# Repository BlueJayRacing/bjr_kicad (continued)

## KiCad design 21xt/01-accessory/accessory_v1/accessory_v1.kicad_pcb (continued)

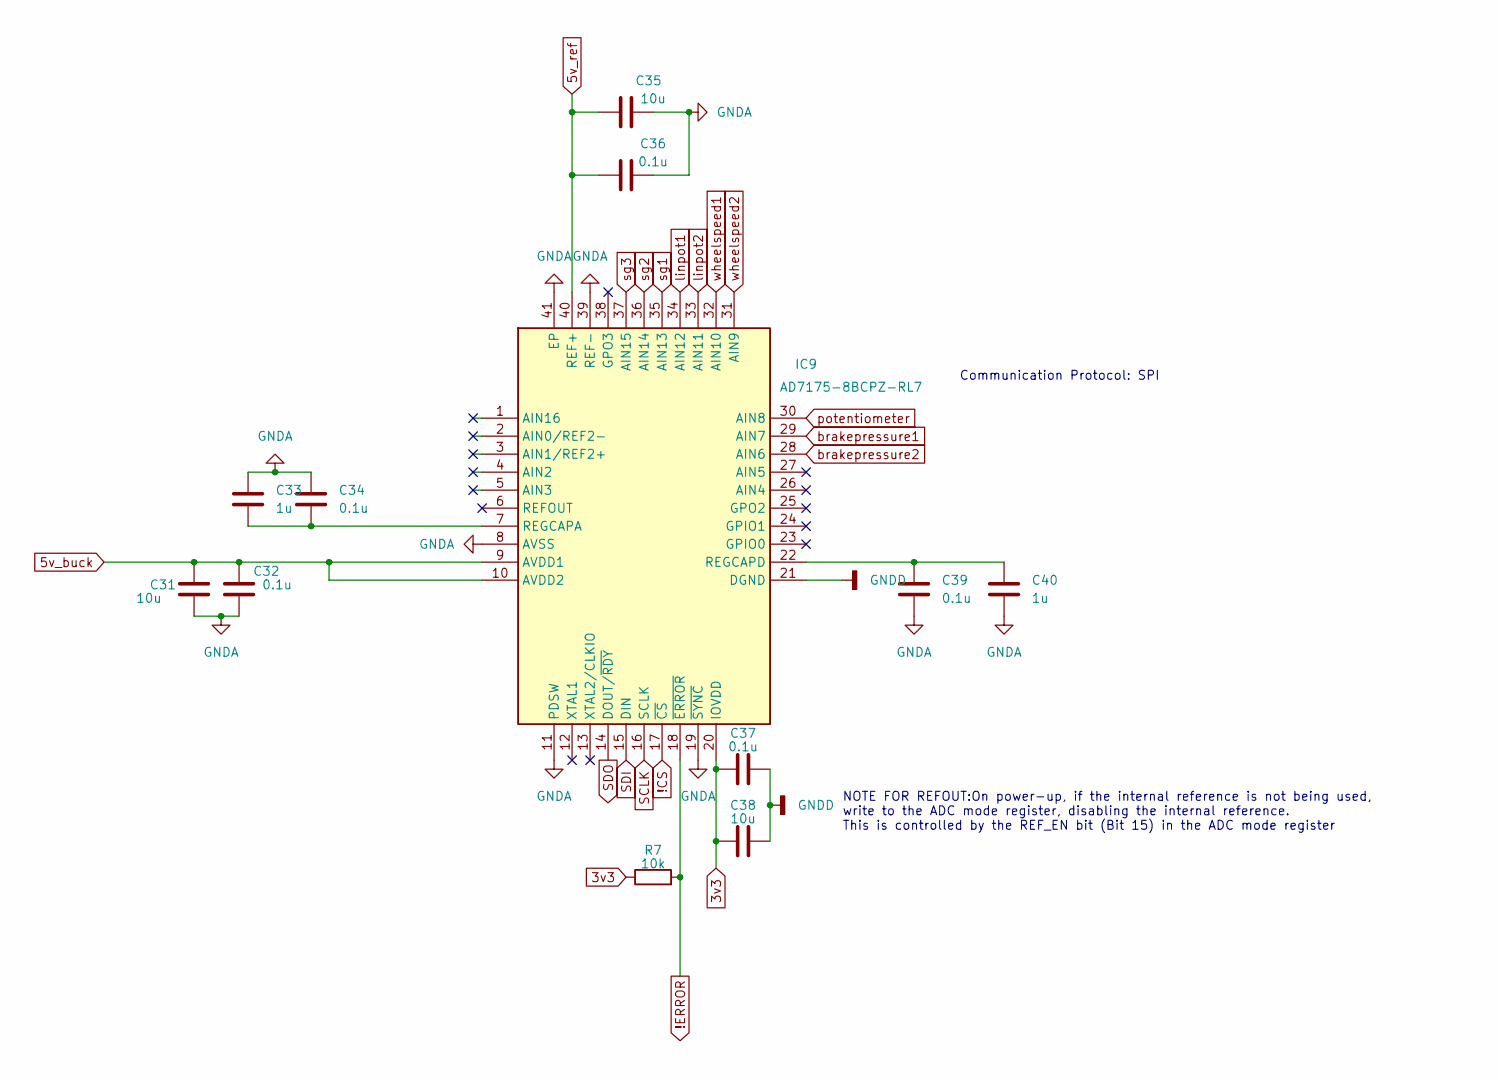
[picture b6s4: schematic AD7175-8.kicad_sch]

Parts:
C31, C35, C38: 10u; C_0603_1608Metric
C32, C34, C36, C37, C39: 0.1u; C_0603_1608Metric
C33, C40: 1u; C_0603_1608Metric
IC9: AD7175-8BCPZ-RL7; QFN50P600X600X80-41N; Mouser Part Number 584-AD7175-8BCPZ-RL7
R7: 10k; R_0603_1608Metric

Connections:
3v3: C37.1, C38.1, IC9.20 (IOVDD), R7.1; also elsewhere on the board
5v_buck: C31.1, C32.1, IC9.9 (AVDD1), IC9.10 (AVDD2); also elsewhere on the board
5v_ref: C35.1, C36.1, IC9.40 (REF+); also elsewhere on the board
!CS: IC9.17 (~CS); also elsewhere on the board
!ERROR: IC9.18 (~ERROR), R7.2; also elsewhere on the board
GNDA: C31.2, C32.2, C33.1, C34.1, C35.2, C36.2, C37.2, C38.2, C39.2, C40.2, IC9.8 (AVSS), IC9.11 (PDSW), IC9.19 (~SYNC), IC9.21 (DGND), IC9.39 (REF-), IC9.41 (EP); also elsewhere on the board
unnamed: C33.2, C34.2, IC9.7 (REGCAPA)
unnamed: C39.1, C40.1, IC9.22 (REGCAPD)
SCLK: IC9.16 (SCLK); also elsewhere on the board
SDI: IC9.15 (DIN); also elsewhere on the board
SDO: IC9.14 (DOUT/~RDY); also elsewhere on the board
brakepressure1: IC9.29 (AIN7); also elsewhere on the board
brakepressure2: IC9.28 (AIN6); also elsewhere on the board
linpot1: IC9.34 (AIN12); also elsewhere on the board
linpot2: IC9.33 (AIN11); also elsewhere on the board
potentiometer: IC9.30 (AIN8); also elsewhere on the board
sg1: IC9.35 (AIN13); also elsewhere on the board
sg2: IC9.36 (AIN14); also elsewhere on the board
sg3: IC9.37 (AIN15); also elsewhere on the board
wheelspeed1: IC9.32 (AIN10); also elsewhere on the board
wheelspeed2: IC9.31 (AIN9); also elsewhere on the board

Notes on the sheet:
NOTE FOR REFOUT:On power-up, if the internal reference is not being used, write to the ADC mode register, disabling the internal reference. This is controlled by the REF_EN bit (Bit 15) in the ADC mode register
Communication Protocol: SPI

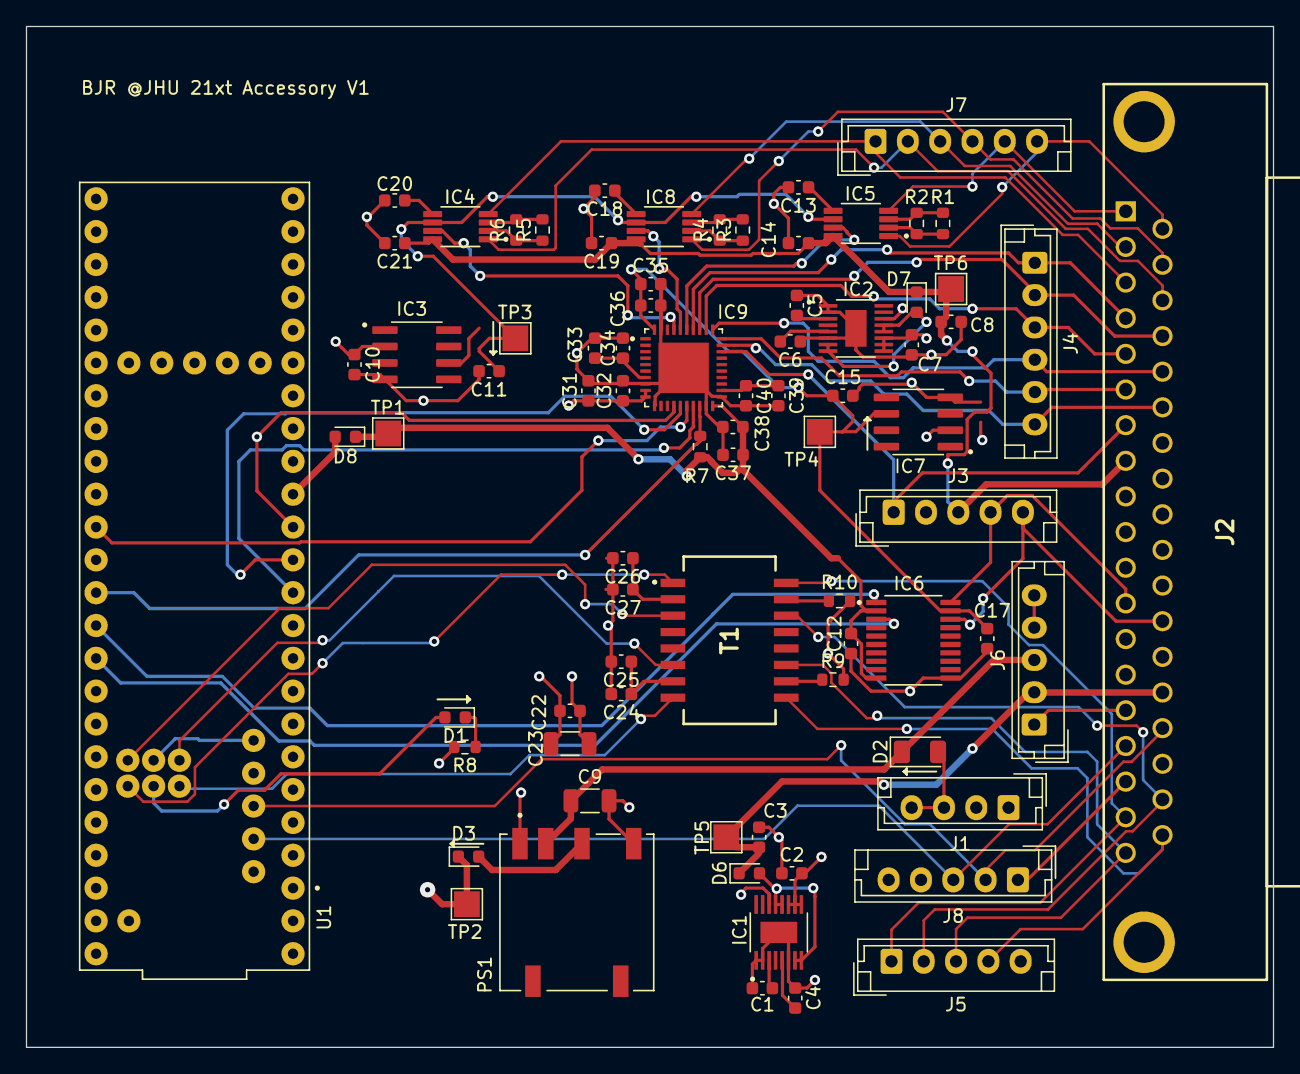
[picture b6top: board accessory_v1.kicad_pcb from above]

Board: 4 copper layers, 96.5 x 79.0 mm, 78 parts (0 on the bottom side), 70 nets.

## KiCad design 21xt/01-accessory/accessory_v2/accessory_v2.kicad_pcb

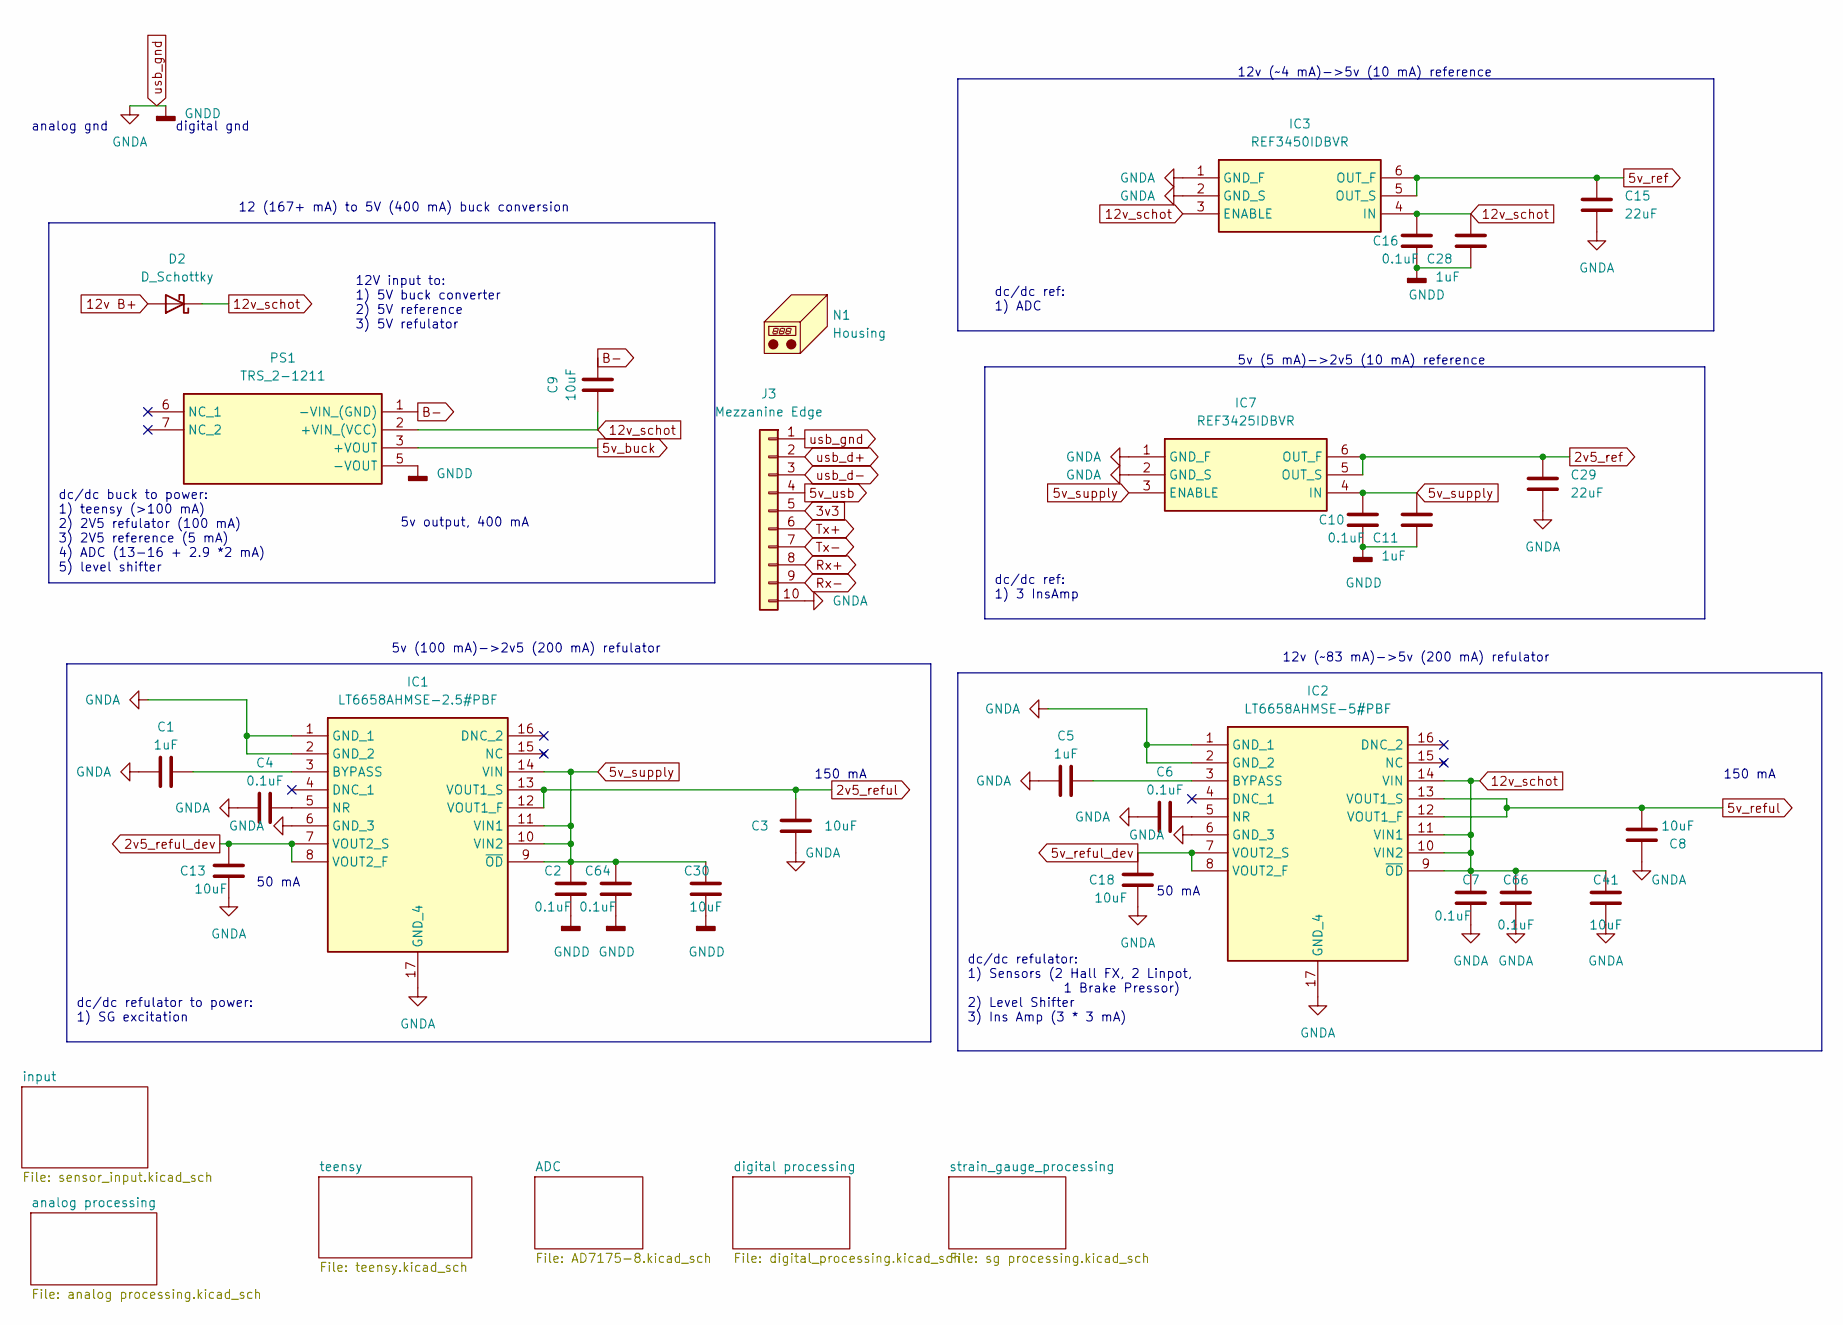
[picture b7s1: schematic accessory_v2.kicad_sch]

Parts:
C1, C5, C11, C28: 1uF; C_0402_1005Metric
C2, C4, C6, C7, C10, C16, C64, C66: 0.1uF; C_0402_1005Metric
C3, C8, C9, C13, C18, C30, C41: 10uF; C_0603_1608Metric
C15, C29: 22uF; C_0603_1608Metric
D2: D_Schottky; D_1206_3216Metric
IC1: LT6658AHMSE-2.5#PBF; SOP50P490X110-17N; Mouser Part Number 584-LT6658AHMSE5PBF
IC2: LT6658AHMSE-5#PBF; SOP50P490X110-17N; Mouser Part Number 584-LT6658AHMSE5PBF
IC3: REF3450IDBVR; Mouser Part Number 595-REF3450IDBVR
IC7: REF3425IDBVR; Mouser Part Number 595-REF3425IDBVR
J3: Mezzanine Edge; Double Sided Mezzanine Card Edge_Edge Side
N1: Housing
PS1: TRS_2-1211; CONV_TRS_2-2419; Mouser Part Number 495-TRS2-1211

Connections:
2v5_ref: C29.1, IC7.5 (OUT_S), IC7.6 (OUT_F); also elsewhere on the board
2v5_reful: C3.2, IC1.12 (VOUT1_F), IC1.13 (VOUT1_S); also elsewhere on the board
2v5_reful_dev: C13.2, IC1.7 (VOUT2_S), IC1.8 (VOUT2_F)
3v3: J3.5; also elsewhere on the board
5v_buck: PS1.3 (+VOUT); also elsewhere on the board
5v_ref: C15.1, IC3.5 (OUT_S), IC3.6 (OUT_F); also elsewhere on the board
5v_reful: C8.2, IC2.12 (VOUT1_F), IC2.13 (VOUT1_S); also elsewhere on the board
5v_reful_dev: C18.2, IC2.7 (VOUT2_S), IC2.8 (VOUT2_F); also elsewhere on the board
5v_supply: C2.2, C10.1, C11.1, C30.2, C64.2, IC1.9 (~OD), IC1.10 (VIN2), IC1.11 (VIN1), IC1.14 (VIN), IC7.3 (ENABLE), IC7.4 (IN); also elsewhere on the board
5v_usb: J3.4; also elsewhere on the board
12v B+: D2.2 (A); also elsewhere on the board
12v_schot: C7.2, C9.1, C16.1, C28.1, C41.2, C66.2, D2.1 (K), IC2.9 (~OD), IC2.10 (VIN2), IC2.11 (VIN1), IC2.14 (VIN), IC3.3 (ENABLE), IC3.4 (IN), PS1.2 (+VIN_(VCC))
B-: C9.2, PS1.1 (-VIN_(GND)); also elsewhere on the board
unnamed: C1.2, IC1.3 (BYPASS)
unnamed: C4.2, IC1.5 (NR)
unnamed: C5.2, IC2.3 (BYPASS)
unnamed: C6.2, IC2.5 (NR)
Rx+: J3.8; also elsewhere on the board
Rx-: J3.9; also elsewhere on the board
Tx+: J3.6; also elsewhere on the board
Tx-: J3.7; also elsewhere on the board
usb_d+: J3.2; also elsewhere on the board
usb_d-: J3.3; also elsewhere on the board
usb_gnd: C1.1, C2.1, C3.1, C4.1, C5.1, C6.1, C7.1, C8.1, C10.2, C11.2, C13.1, C15.2, C16.2, C18.1, C28.2, C29.2, C30.1, C41.1, C64.1, C66.1, IC1.1 (GND_1), IC1.2 (GND_2), IC1.6 (GND_3), IC1.17 (GND_4), IC2.1 (GND_1), IC2.2 (GND_2), IC2.6 (GND_3), IC2.17 (GND_4), IC3.1 (GND_F), IC3.2 (GND_S), IC7.1 (GND_F), IC7.2 (GND_S), J3.1, J3.10, PS1.5 (-VOUT); also elsewhere on the board

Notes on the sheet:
dc/dc refulator to power: 1) SG excitation
dc/dc ref: 1) 3 InsAmp
150 mA
50 mA
5v (5 mA)->2v5 (10 mA) reference
analog gnd
dc/dc ref: 1) ADC
12 (167+ mA) to 5V (400 mA) buck conversion
12V input to: 1) 5V buck converter 2) 5V reference 3) 5V refulator
5v (100 mA)->2v5 (200 mA) refulator
12v (~83 mA)->5v (200 mA) refulator
digital gnd
dc/dc refulator: 1) Sensors (2 Hall FX, 2 Linpot, 1 Brake Pressor) 2) Level Shifter 3) Ins Amp (3 * 3 mA)
dc/dc buck to power: 1) teensy (>100 mA) 2) 2V5 refulator (100 mA) 3) 2V5 reference (5 mA) 4) ADC (13-16 + 2.9 *2 mA) 5) level shifter
5v output, 400 mA
150 mA
12v (~4 mA)->5v (10 mA) reference

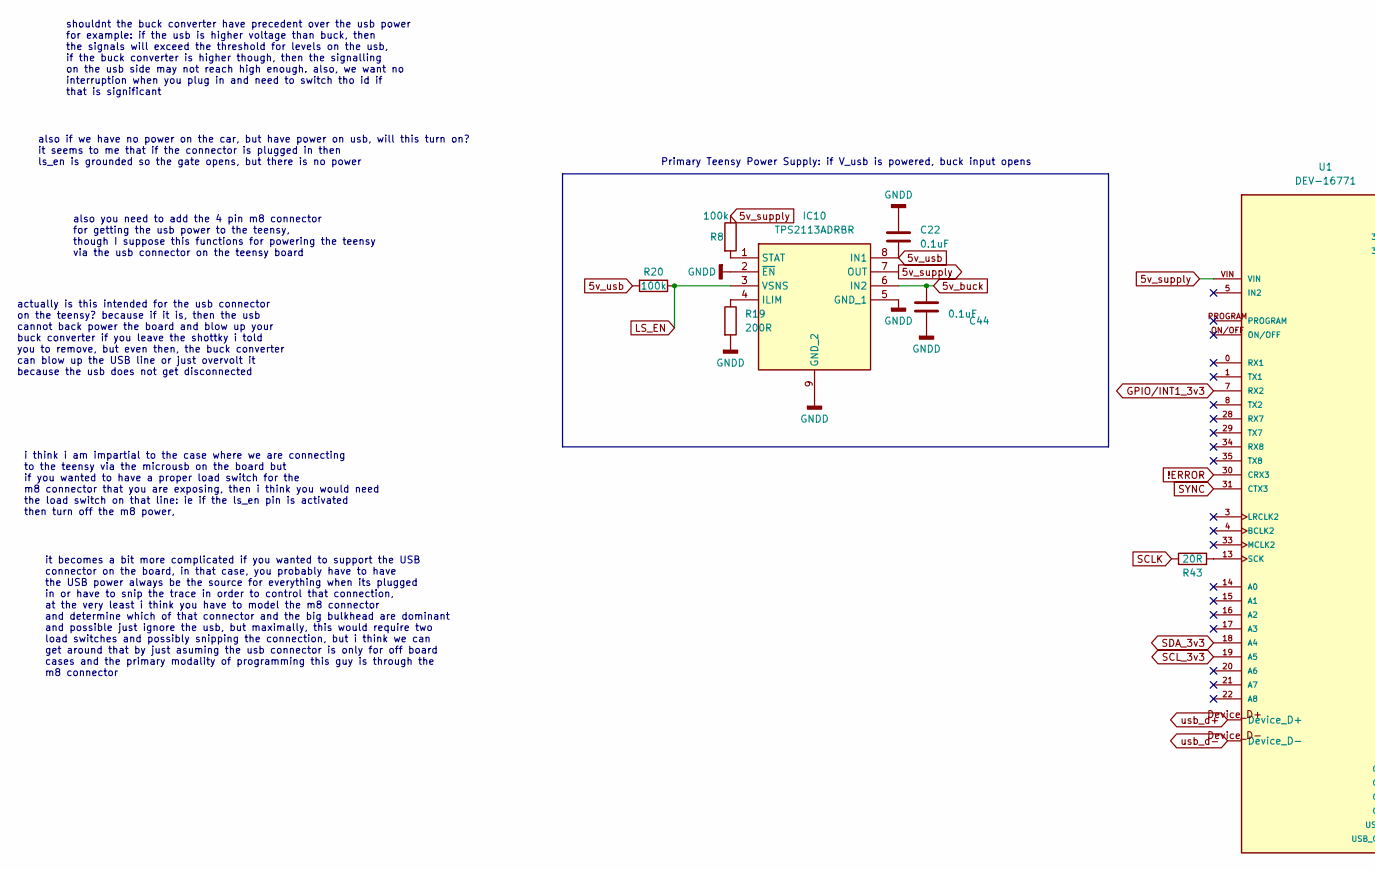
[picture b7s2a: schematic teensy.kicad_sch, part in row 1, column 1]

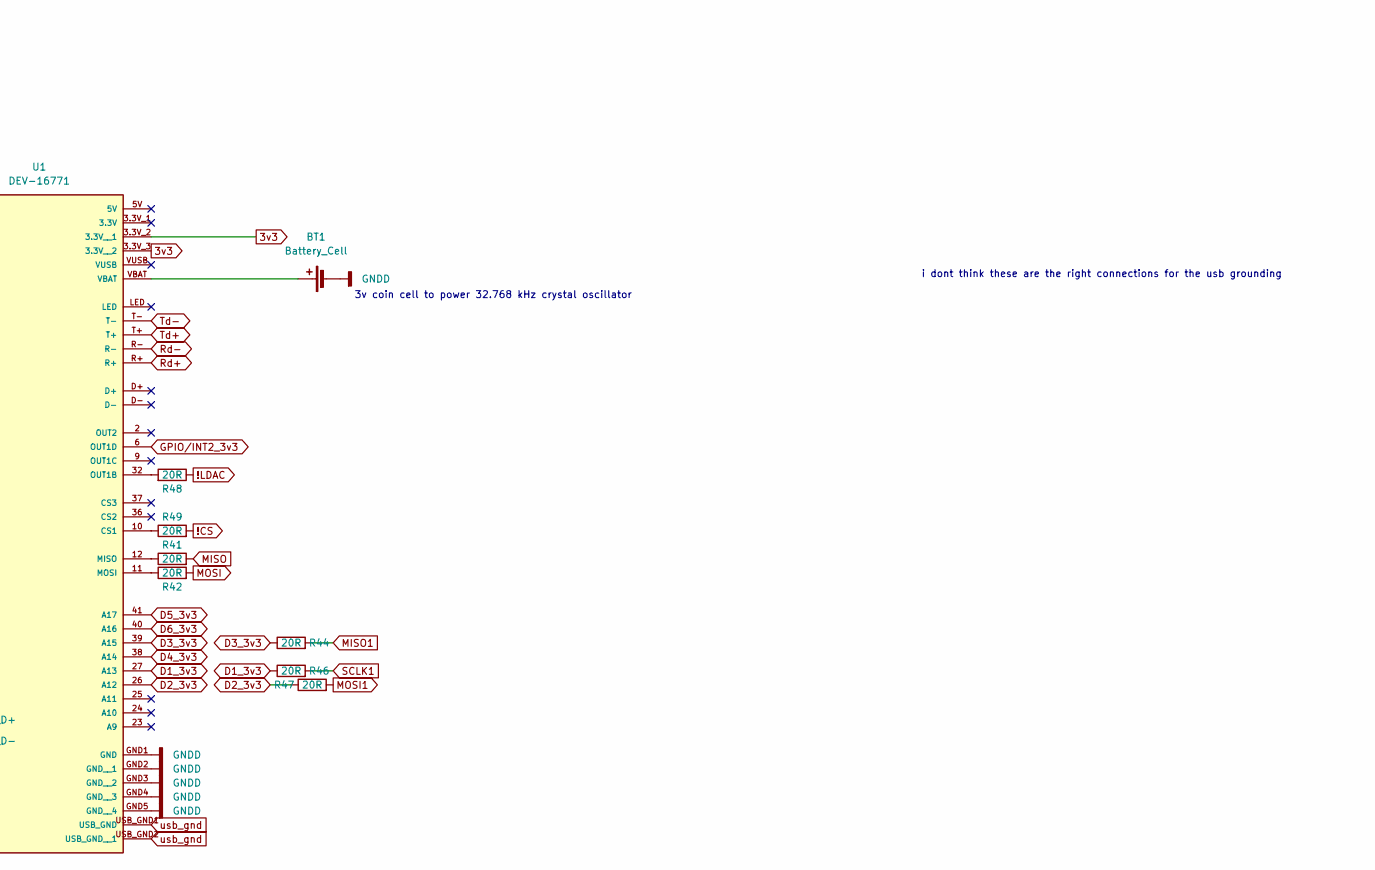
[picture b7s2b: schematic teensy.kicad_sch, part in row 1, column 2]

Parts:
BT1: Battery_Cell; 1220 holder
C22, C44: 0.1uF; C_0402_1005Metric
IC10: TPS2113ADRBR; Mouser Part Number 595-TPS2113ADRBR
R8, R20: 100k; R_0402_1005Metric
R19: 200R; R_0402_1005Metric
R41, R42, R43, R44, R46, R47, R48, R49: 20R; R_0402_1005Metric
U1: DEV-16771; MODULE_DEV-16771; PARTREV 4.1

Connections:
3v3: U1.3.3V_2 (3.3V__1), U1.3.3V_3 (3.3V__2); also elsewhere on the board
5v_buck: C44.1, IC10.6 (IN2); also elsewhere on the board
5v_supply: IC10.7 (OUT), R8.1, U1.VIN; also elsewhere on the board
5v_usb: C22.2, IC10.8 (IN1), R20.2; also elsewhere on the board
!CS: R49.2; also elsewhere on the board
!ERROR: U1.30 (CRX3); also elsewhere on the board
!LDAC: R48.1; also elsewhere on the board
D1_3v3: R46.1, U1.27 (A13); also elsewhere on the board
D2_3v3: R47.1, U1.26 (A12); also elsewhere on the board
D3_3v3: R44.1, U1.39 (A15); also elsewhere on the board
D4_3v3: U1.38 (A14); also elsewhere on the board
D5_3v3: U1.41 (A17); also elsewhere on the board
D6_3v3: U1.40 (A16); also elsewhere on the board
GPIO/INT1_3v3: U1.7 (RX2); also elsewhere on the board
GPIO/INT2_3v3: U1.6 (OUT1D); also elsewhere on the board
LS_EN: IC10.3 (VSNS), R20.1; also elsewhere on the board
MISO: R41.2; also elsewhere on the board
MISO1: R44.2; also elsewhere on the board
MOSI: R42.2; also elsewhere on the board
MOSI1: R47.2; also elsewhere on the board
unnamed: BT1.1 (+), U1.VBAT
unnamed: IC10.4 (ILIM), R19.1
unnamed: IC10.1 (STAT), R8.2
unnamed: R49.1, U1.10 (CS1)
unnamed: R41.1, U1.12 (MISO)
unnamed: R42.1, U1.11 (MOSI)
unnamed: R48.2, U1.32 (OUT1B)
unnamed: R43.2, U1.13 (SCK)
Rd+: U1.R+; also elsewhere on the board
Rd-: U1.R-; also elsewhere on the board
SCLK: R43.1; also elsewhere on the board
SCLK1: R46.2; also elsewhere on the board
SCL_3v3: U1.19 (A5); also elsewhere on the board
SDA_3v3: U1.18 (A4); also elsewhere on the board
SYNC: U1.31 (CTX3); also elsewhere on the board
Td+: U1.T+; also elsewhere on the board
Td-: U1.T-; also elsewhere on the board
usb_d+: U1.Device_D+; also elsewhere on the board
usb_d-: U1.Device_D-; also elsewhere on the board
usb_gnd: BT1.2 (-), C22.1, C44.2, IC10.2 (~EN), IC10.5 (GND_1), IC10.9 (GND_2), R19.2, U1.GND1 (GND), U1.GND2 (GND__1), U1.GND3 (GND__2), U1.GND4 (GND__3), U1.GND5 (GND__4), U1.USB_GND1 (USB_GND), U1.USB_GND2 (USB_GND__1); also elsewhere on the board

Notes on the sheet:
Primary Teensy Power Supply: if V_usb is powered, buck input opens
3v coin cell to power 32.768 kHz crystal oscillator
it becomes a bit more complicated if you wanted to support the USB connector on the board, in that case, you probably have to have the USB power always be the source for everything when its plugged in or have to snip the trace in order to control that connection, at the very least i think you have 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
shouldnt the buck converter have precedent over the usb power for example: if the usb is higher voltage than buck, then the signals will exceed the threshold for levels on the usb, if the buck converter is higher though, then the signalling on the usb side may not reach high enough. also, we want n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
actually is this intended for the usb connector on the teensy? because if it is, then the usb cannot back power the board and blow up your buck converter if you leave the shottky i told you to remove, but even then, the buck converter can blow up the USB line or just overvolt it because the usb doe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
also you need to add the 4 pin m8 connector for getting the usb power to the teensy, though I suppose this functions for powering the teensy via the usb connector on the teensy board
i think i am impartial to the case where we are connecting to the teensy via the microusb on the board but if you wanted to have a proper load switch for the m8 connector that you are exposing, then i think you would need the load switch on that line: ie if the ls_en pin is activated then turn off 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
i dont think these are the right connections for the usb grounding
also if we have no power on the car, but have power on usb, will this turn on? it seems to me that if the connector is plugged in then ls_en is grounded so the gate opens, but there is no power

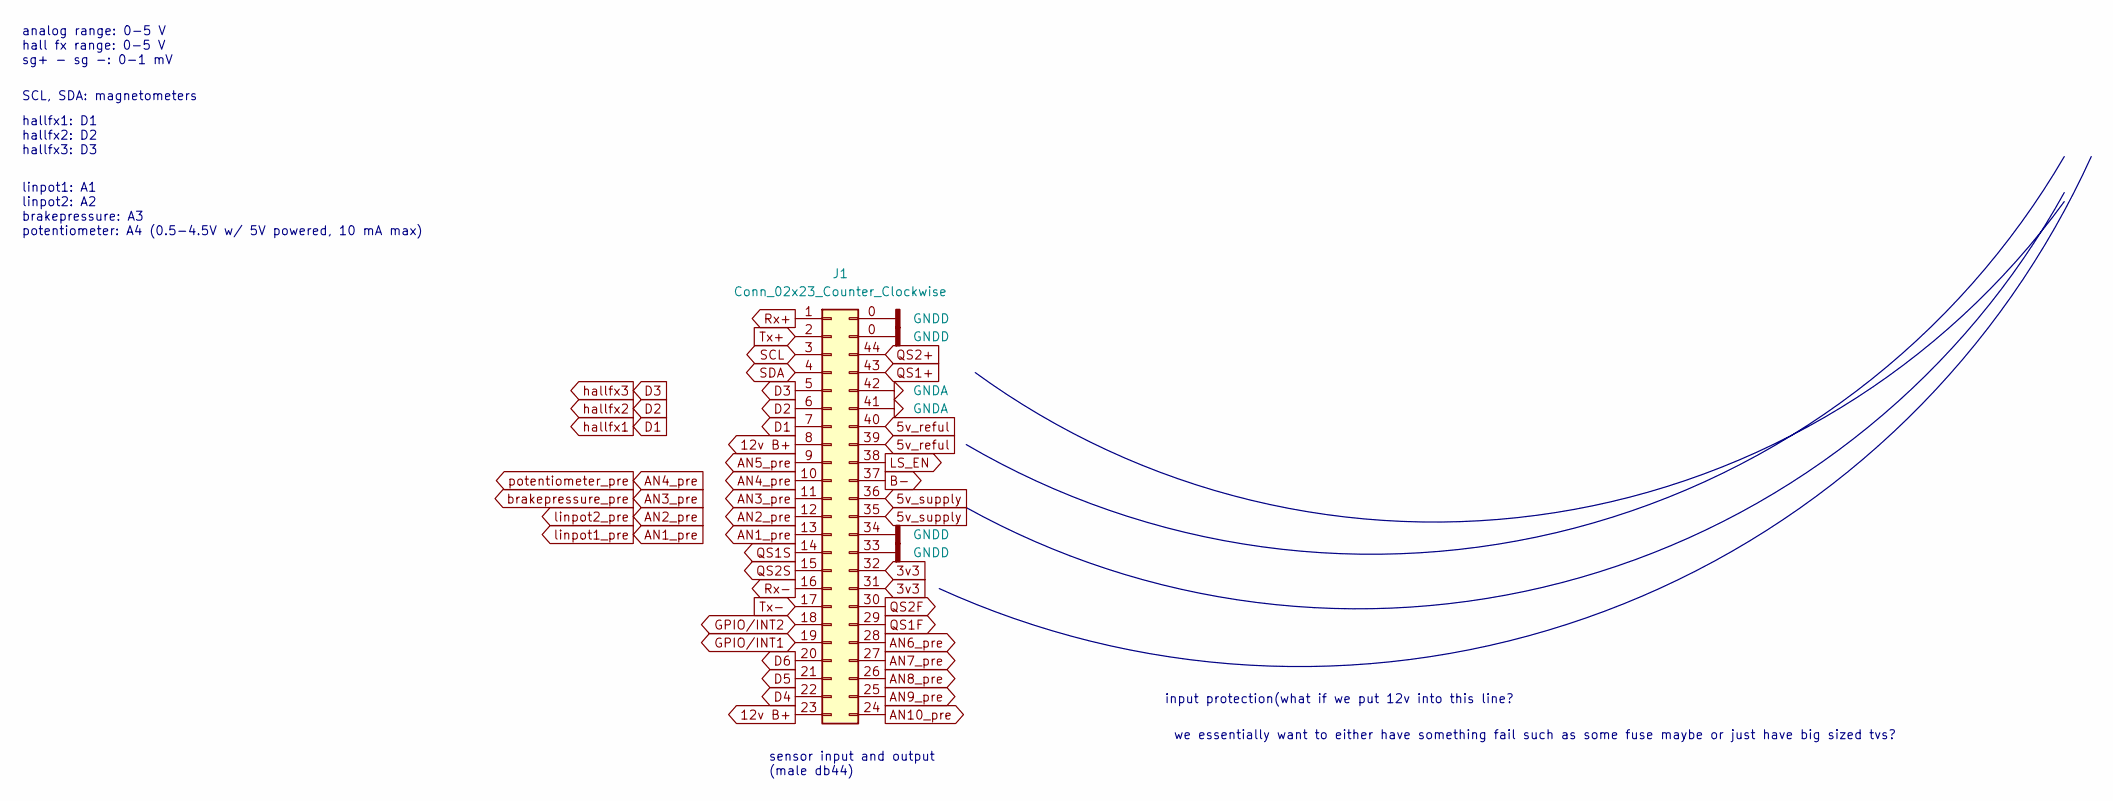
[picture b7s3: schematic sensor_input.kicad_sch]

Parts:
J1: Conn_02x23_Counter_Clockwise; aaren_mouser_db44_screws

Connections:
2v5_reful: J1.43, J1.44; also elsewhere on the board
3v3: J1.31, J1.32; also elsewhere on the board
5v_reful: J1.39, J1.40; also elsewhere on the board
5v_supply: J1.35, J1.36; also elsewhere on the board
12v B+: J1.8, J1.23; also elsewhere on the board
AN1_pre: J1.13; also elsewhere on the board
AN2_pre: J1.12; also elsewhere on the board
AN3_pre: J1.11; also elsewhere on the board
AN4_pre: J1.10; also elsewhere on the board
AN5_pre: J1.9; also elsewhere on the board
AN6_pre: J1.28; also elsewhere on the board
AN7_pre: J1.27; also elsewhere on the board
AN8_pre: J1.26; also elsewhere on the board
AN9_pre: J1.25; also elsewhere on the board
AN10_pre: J1.24; also elsewhere on the board
B-: J1.37; also elsewhere on the board
D1: J1.7; also elsewhere on the board
D2: J1.6; also elsewhere on the board
D3: J1.5; also elsewhere on the board
D4: J1.22; also elsewhere on the board
D5: J1.21; also elsewhere on the board
D6: J1.20; also elsewhere on the board
GPIO/INT1: J1.19; also elsewhere on the board
GPIO/INT2: J1.18; also elsewhere on the board
LS_EN: J1.38; also elsewhere on the board
QS1F: J1.29; also elsewhere on the board
QS1S: J1.14; also elsewhere on the board
QS2F: J1.30; also elsewhere on the board
QS2S: J1.15; also elsewhere on the board
Rx+: J1.1; also elsewhere on the board
Rx-: J1.16; also elsewhere on the board
SCL: J1.3; also elsewhere on the board
SDA: J1.4; also elsewhere on the board
Tx+: J1.2; also elsewhere on the board
Tx-: J1.17; also elsewhere on the board
usb_gnd: J1.0 (Pin_45), J1.33, J1.34, J1.41, J1.42; also elsewhere on the board

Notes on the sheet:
SCL, SDA: magnetometers
sensor input and output (male db44)
analog range: 0-5 V hall fx range: 0-5 V sg+ - sg -: 0-1 mV
linpot1: A1 linpot2: A2 brakepressure: A3 potentiometer: A4 (0.5-4.5V w/ 5V powered, 10 mA max)
we essentially want to either have something fail such as some fuse maybe or just have big sized tvs?
hallfx1: D1 hallfx2: D2 hallfx3: D3
input protection(what if we put 12v into this line?

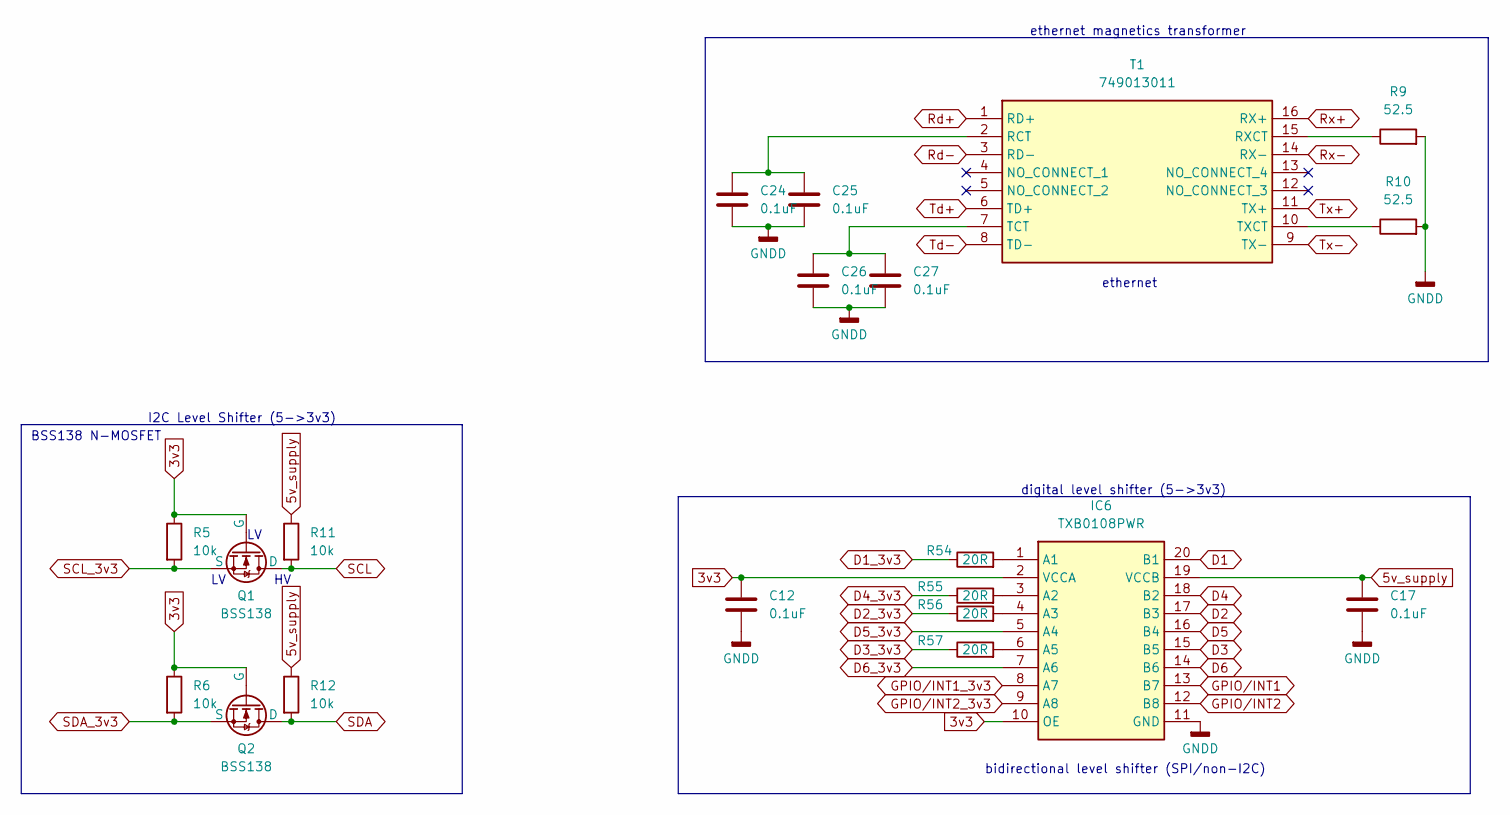
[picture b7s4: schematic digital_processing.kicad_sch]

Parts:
C12, C17, C24, C25, C26, C27: 0.1uF; C_0402_1005Metric
IC6: TXB0108PWR; SOP65P640X120-20N; Mouser Part Number 595-TXB0108PWR
Q1, Q2: BSS138; SOT-23-3
R5, R6, R11, R12: 10k; R_0402_1005Metric
R9, R10: 52.5; R_0402_1005Metric
R54, R55, R56, R57: 20R; R_0402_1005Metric
T1: 749013011; Mouser Part Number 710-749013011

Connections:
3v3: C12.1, IC6.2 (VCCA), IC6.10 (OE), Q1.2 (G), Q2.2 (G), R5.1, R6.1; also elsewhere on the board
5v_supply: C17.1, IC6.19 (VCCB), R11.1, R12.1; also elsewhere on the board
D1: IC6.20 (B1); also elsewhere on the board
D1_3v3: R54.1; also elsewhere on the board
D2: IC6.17 (B3); also elsewhere on the board
D2_3v3: R56.1; also elsewhere on the board
D3: IC6.15 (B5); also elsewhere on the board
D3_3v3: R57.1; also elsewhere on the board
D4: IC6.18 (B2); also elsewhere on the board
D4_3v3: R55.1; also elsewhere on the board
D5: IC6.16 (B4); also elsewhere on the board
D5_3v3: IC6.5 (A4); also elsewhere on the board
D6: IC6.14 (B6); also elsewhere on the board
D6_3v3: IC6.7 (A6); also elsewhere on the board
GPIO/INT1: IC6.13 (B7); also elsewhere on the board
GPIO/INT1_3v3: IC6.8 (A7); also elsewhere on the board
GPIO/INT2: IC6.12 (B8); also elsewhere on the board
GPIO/INT2_3v3: IC6.9 (A8); also elsewhere on the board
unnamed: IC6.1 (A1), R54.2
unnamed: IC6.3 (A2), R55.2
unnamed: IC6.4 (A3), R56.2
unnamed: IC6.6 (A5), R57.2
unnamed: C24.1, C25.1, T1.2 (RCT)
unnamed: R9.1, T1.15 (RXCT)
unnamed: C26.1, C27.1, T1.7 (TCT)
unnamed: R10.1, T1.10 (TXCT)
Rd+: T1.1 (RD+); also elsewhere on the board
Rd-: T1.3 (RD-); also elsewhere on the board
Rx+: T1.16 (RX+); also elsewhere on the board
Rx-: T1.14 (RX-); also elsewhere on the board
SCL: Q1.1 (D), R11.2; also elsewhere on the board
SCL_3v3: Q1.3 (S), R5.2; also elsewhere on the board
SDA: Q2.1 (D), R12.2; also elsewhere on the board
SDA_3v3: Q2.3 (S), R6.2; also elsewhere on the board
Td+: T1.6 (TD+); also elsewhere on the board
Td-: T1.8 (TD-); also elsewhere on the board
Tx+: T1.11 (TX+); also elsewhere on the board
Tx-: T1.9 (TX-); also elsewhere on the board
usb_gnd: C12.2, C17.2, C24.2, C25.2, C26.2, C27.2, IC6.11 (GND), R9.2, R10.2; also elsewhere on the board

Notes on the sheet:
I2C Level Shifter (5->3v3)
ethernet magnetics transformer
digital level shifter (5->3v3)
bidirectional level shifter (SPI/non-I2C)
BSS138 N-MOSFET
ethernet

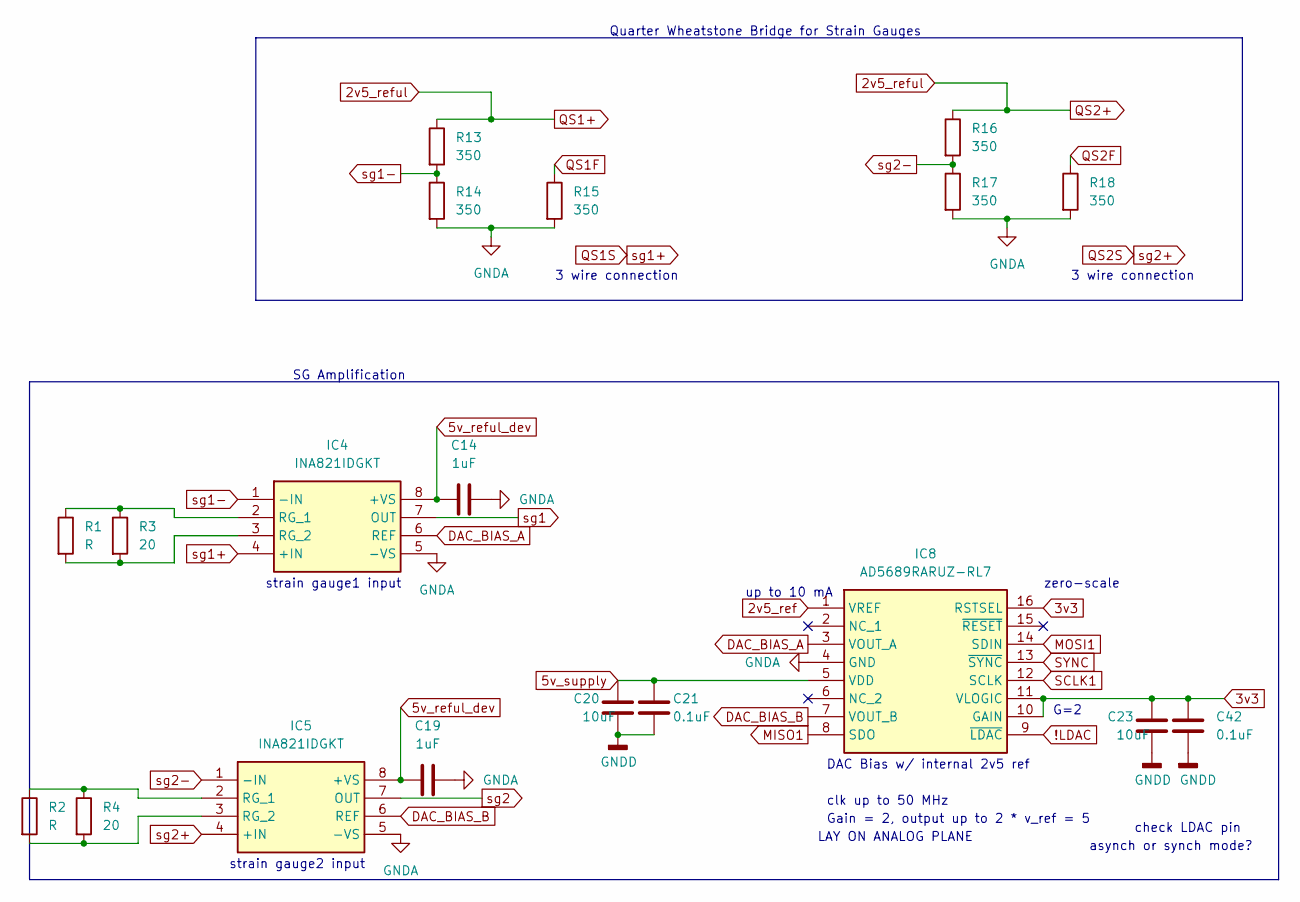
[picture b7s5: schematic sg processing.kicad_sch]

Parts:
C14, C19: 1uF; C_0402_1005Metric
C20, C23: 10uF; C_0603_1608Metric
C21, C42: 0.1uF; C_0402_1005Metric
IC4, IC5: INA821IDGKT; SOP65P490X110-8N; Mouser Part Number 595-INA821IDGKT
IC8: AD5689RARUZ-RL7; SOP65P640X120-16N; Mouser Part Number 584-AD5689RARUZ-R7
R1, R2: R; R_0402_1005Metric
R3, R4: 20; R_0402_1005Metric
R13, R14, R15, R16, R17, R18: 350; R_0402_1005Metric

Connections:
2v5_ref: IC8.1 (VREF); also elsewhere on the board
2v5_reful: R13.1, R16.1; also elsewhere on the board
3v3: C23.1, C42.1, IC8.10 (GAIN), IC8.11 (VLOGIC), IC8.16 (RSTSEL); also elsewhere on the board
5v_reful_dev: C14.1, C19.1, IC4.8 (+VS), IC5.8 (+VS); also elsewhere on the board
5v_supply: C20.1, C21.1, IC8.5 (VDD); also elsewhere on the board
!LDAC: IC8.9 (~LDAC); also elsewhere on the board
DAC_BIAS_A: IC4.6 (REF), IC8.3 (VOUT_A)
DAC_BIAS_B: IC5.6 (REF), IC8.7 (VOUT_B)
MISO1: IC8.8 (SDO); also elsewhere on the board
MOSI1: IC8.14 (SDIN); also elsewhere on the board
unnamed: IC4.2 (RG_1), R1.1, R3.1
unnamed: IC4.3 (RG_2), R1.2, R3.2
unnamed: IC5.2 (RG_1), R2.1, R4.1
unnamed: IC5.3 (RG_2), R2.2, R4.2
QS1F: R15.1; also elsewhere on the board
QS1S: IC4.4 (+IN); also elsewhere on the board
QS2F: R18.1; also elsewhere on the board
QS2S: IC5.4 (+IN); also elsewhere on the board
SCLK1: IC8.12 (SCLK); also elsewhere on the board
SYNC: IC8.13 (~SYNC); also elsewhere on the board
sg1: IC4.7 (OUT); also elsewhere on the board
sg1-: IC4.1 (-IN), R13.2, R14.1
sg2: IC5.7 (OUT); also elsewhere on the board
sg2-: IC5.1 (-IN), R16.2, R17.1
usb_gnd: C14.2, C19.2, C20.2, C21.2, C23.2, C42.2, IC4.5 (-VS), IC5.5 (-VS), IC8.4 (GND), R14.2, R15.2, R17.2, R18.2; also elsewhere on the board

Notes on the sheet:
clk up to 50 MHz
check LDAC pin
LAY ON ANALOG PLANE
Gain = 2, output up to 2 * v_ref = 5
SG Amplification
strain gauge2 input
zero-scale
asynch or synch mode?
3 wire connection
up to 10 mA
Quarter Wheatstone Bridge for Strain Gauges
DAC Bias w/ internal 2v5 ref
G=2
strain gauge1 input
